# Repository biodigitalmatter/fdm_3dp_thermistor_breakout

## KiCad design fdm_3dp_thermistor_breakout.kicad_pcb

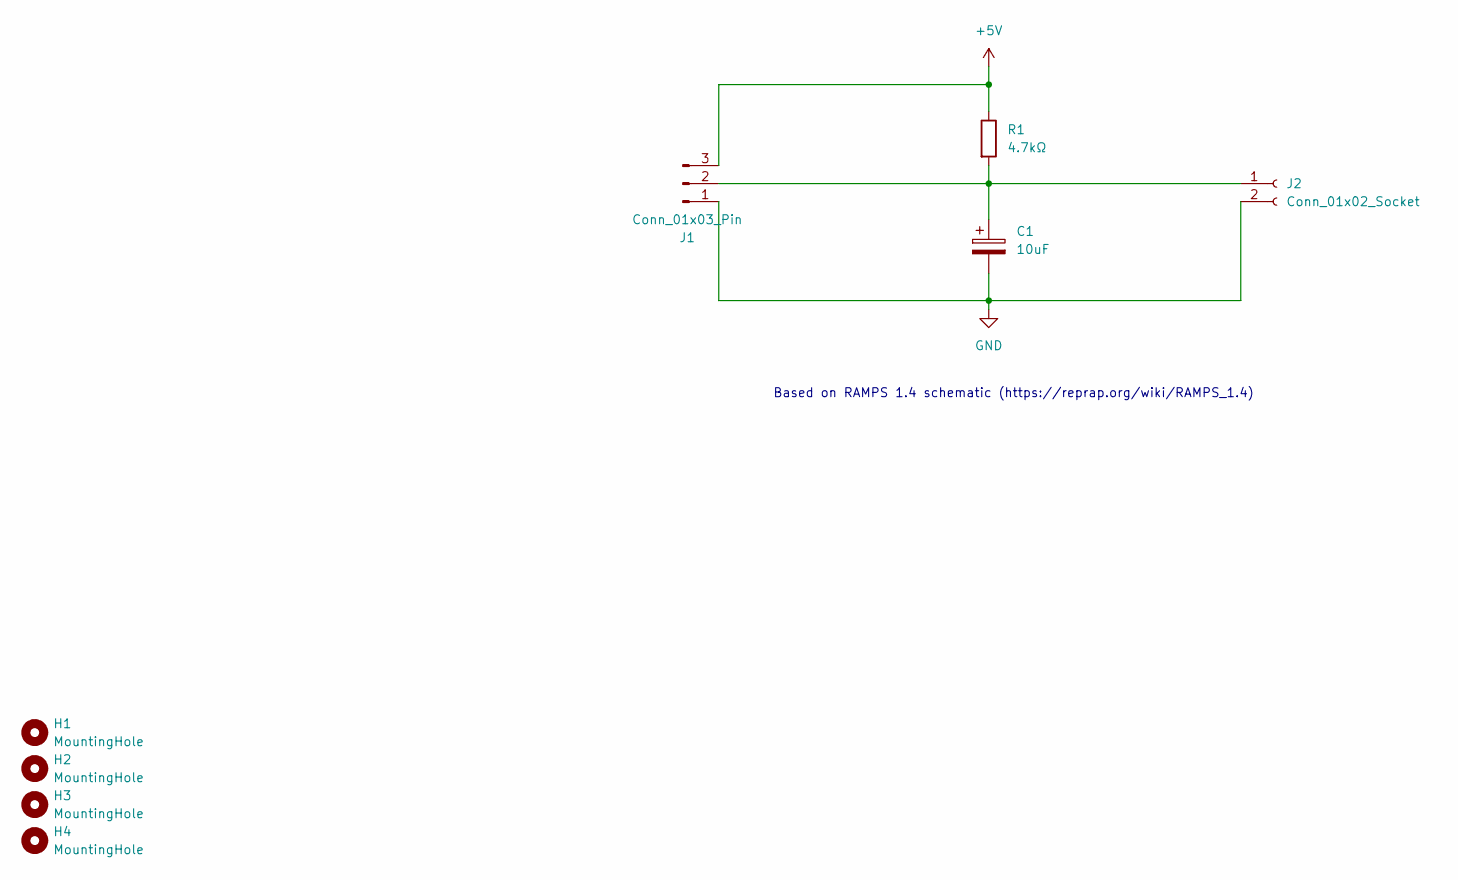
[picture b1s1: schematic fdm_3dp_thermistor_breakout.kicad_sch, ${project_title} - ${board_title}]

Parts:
C1: 10uF; CP_Radial_D6.3mm_P2.50mm
H1, H2, H3, H4: MountingHole; MountingHole_2.2mm_M2
J1: Conn_01x03_Pin; Molex_Micro-Fit_3.0_43650-0315_1x03_P3.00mm_Vertical
J2: Conn_01x02_Socket; Molex_Micro-Fit_3.0_43650-0215_1x02_P3.00mm_Vertical
R1: 4.7kΩ; R_Axial_DIN0204_L3.6mm_D1.6mm_P5.08mm_Horizontal

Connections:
+5V: J1.3, R1.1
GND: C1.2, J1.1, J2.2
unnamed: C1.1, J1.2, J2.1, R1.2

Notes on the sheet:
Based on RAMPS 1.4 schematic (https://reprap.org/wiki/RAMPS_1.4)

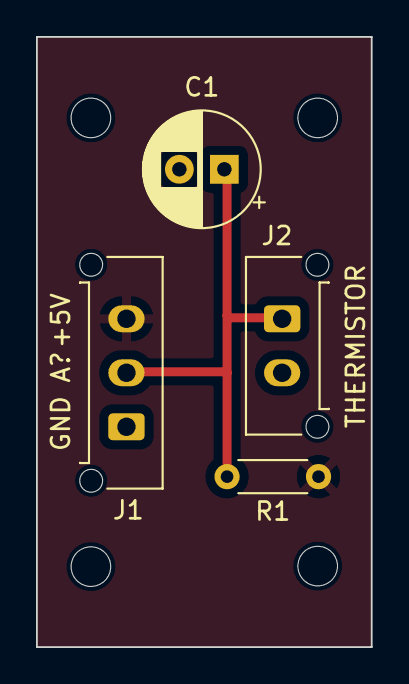
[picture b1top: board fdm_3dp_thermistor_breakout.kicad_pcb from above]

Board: 2 copper layers, 18.6 x 33.9 mm, 8 parts (0 on the bottom side), 3 nets.

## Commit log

2023-10-19 setup and upload of ordered pcb
2023-10-30 parts sourced
